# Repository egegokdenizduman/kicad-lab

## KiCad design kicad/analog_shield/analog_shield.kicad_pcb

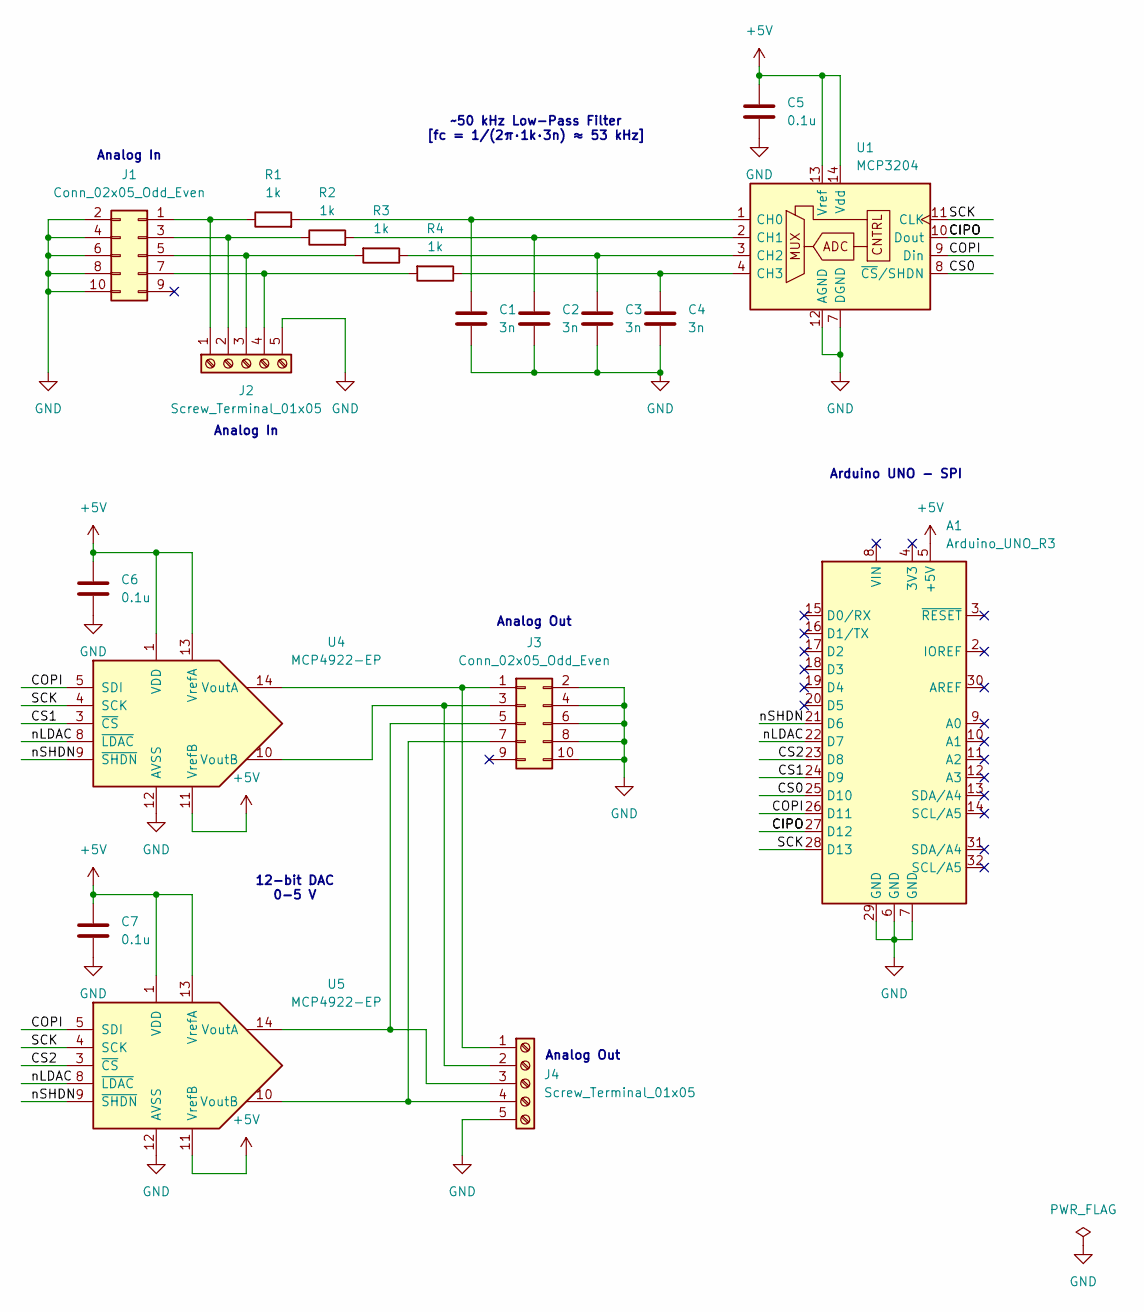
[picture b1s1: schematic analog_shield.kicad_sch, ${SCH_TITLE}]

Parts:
A1: Arduino_UNO_R3
C1, C2, C3, C4: 3n; C_Disc_D5.0mm_W2.5mm_P5.00mm
C5, C6, C7: 0.1u; C_Disc_D5.0mm_W2.5mm_P5.00mm
J1, J3: Conn_02x05_Odd_Even; PinSocket_2x05_P2.54mm_Vertical
J2, J4: Screw_Terminal_01x05; TerminalBlock_Xinya_XY308-2.54-5P_1x05_P2.54mm_Horizontal
R1, R2, R3, R4: 1k; R_Axial_DIN0207_L6.3mm_D2.5mm_P10.16mm_Horizontal
U1: MCP3204; DIP-14_W7.62mm
U4, U5: MCP4922-EP; DIP-14_W7.62mm

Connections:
+5V: A1.5 (+5V), C5.2, C6.2, C7.1, U1.13 (Vref), U1.14 (Vdd), U4.1 (VDD), U4.11 (VrefB), U4.13 (VrefA), U5.1 (VDD), U5.11 (VrefB), U5.13 (VrefA)
/CIPO: A1.27 (D12), U1.10 (Dout)
/COPI: A1.26 (D11), U1.9 (Din), U4.5 (SDI), U5.5 (SDI)
/CS0: A1.25 (D10), U1.8 (~CS/SHDN)
/CS1: A1.24 (D9), U4.3 (~CS)
/CS2: A1.23 (D8), U5.3 (~CS)
/SCK: A1.28 (D13), U1.11 (CLK), U4.4 (SCK), U5.4 (SCK)
/nLDAC: A1.22 (D7), U4.8 (~LDAC), U5.8 (~LDAC)
/nSHDN: A1.21 (D6), U4.9 (~SHDN), U5.9 (~SHDN)
GND: A1.6 (GND), A1.7 (GND), A1.29 (GND), C1.2, C2.2, C3.2, C4.2, C5.1, C6.1, C7.2, J1.2, J1.4, J1.6, J1.8, J1.10, J2.5, J3.2, J3.4, J3.6, J3.8, J3.10, J4.5, U1.7 (DGND), U1.12 (AGND), U4.12 (AVSS), U5.12 (AVSS)
unnamed: J1.1, J2.1, R1.1
unnamed: J1.3, J2.2, R2.1
unnamed: J1.5, J2.3, R3.2
unnamed: J1.7, J2.4, R4.2
unnamed: J3.1, J4.1, U4.14 (VoutA)
unnamed: J3.3, J4.2, U4.10 (VoutB)
unnamed: J3.5, J4.3, U5.14 (VoutA)
unnamed: J3.7, J4.4, U5.10 (VoutB)
unnamed: C1.1, R1.2, U1.1 (CH0)
unnamed: C2.1, R2.2, U1.2 (CH1)
unnamed: C3.1, R3.1, U1.3 (CH2)
unnamed: C4.1, R4.1, U1.4 (CH3)

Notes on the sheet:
Analog In
12-bit DAC 0-5 V
Analog Out
~50 kHz Low-Pass Filter [fc = 1/(2π·1k·3n) ≈ 53 kHz]
Arduino UNO - SPI

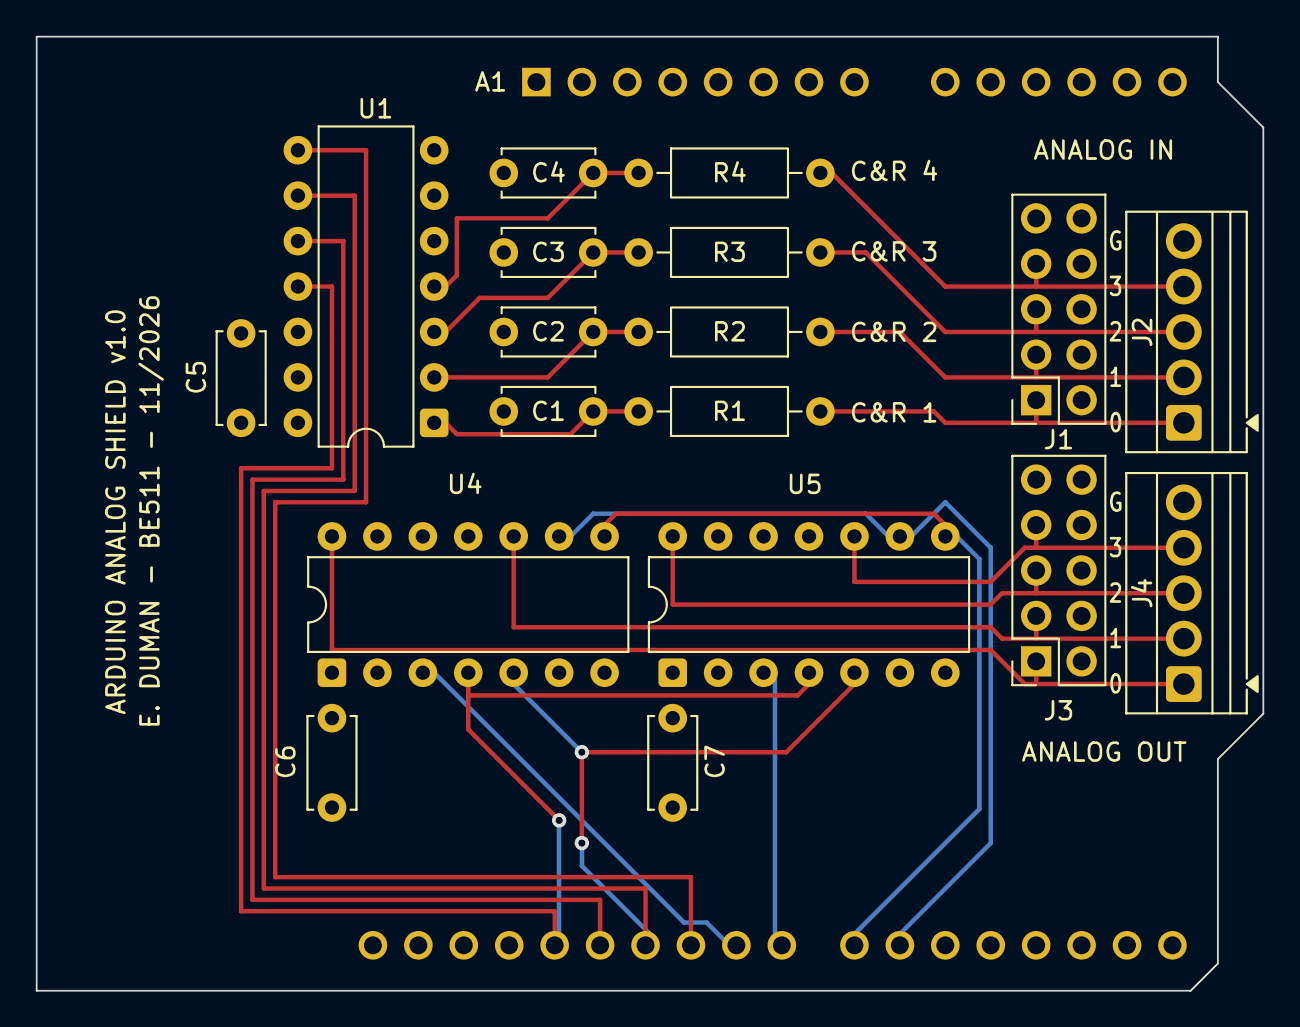
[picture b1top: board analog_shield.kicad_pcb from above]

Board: 4 copper layers, 68.6 x 53.3 mm, 19 parts (0 on the bottom side), 22 nets.
